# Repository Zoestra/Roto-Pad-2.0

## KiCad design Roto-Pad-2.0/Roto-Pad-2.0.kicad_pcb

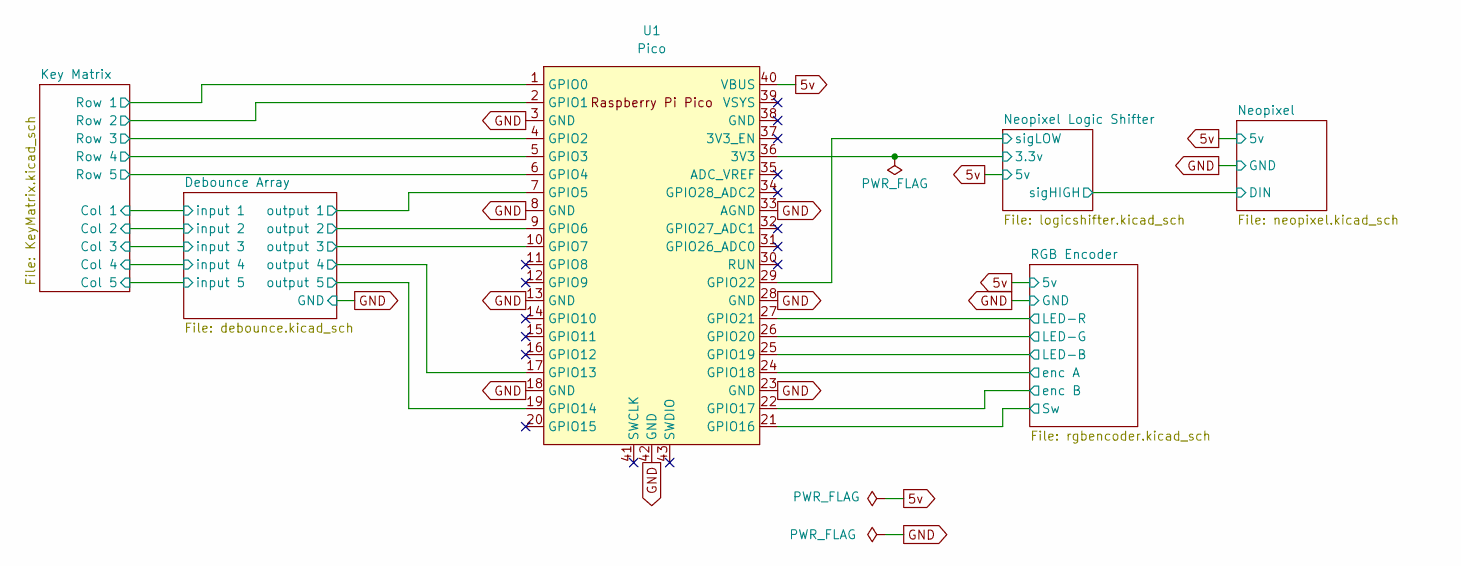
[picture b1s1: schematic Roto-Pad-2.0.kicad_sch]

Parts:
U1: Pico; raspberry_pi_pico_THT

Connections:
5v: U1.40 (VBUS); also elsewhere on the board
/Debounce Array/output 1: U1.7 (GPIO5); also elsewhere on the board
/Debounce Array/output 2: U1.9 (GPIO6); also elsewhere on the board
/Debounce Array/output 3: U1.10 (GPIO7); also elsewhere on the board
/Debounce Array/output 4: U1.17 (GPIO13); also elsewhere on the board
/Debounce Array/output 5: U1.19 (GPIO14); also elsewhere on the board
/Key Matrix/Row 1: U1.1 (GPIO0); also elsewhere on the board
/Key Matrix/Row 2: U1.2 (GPIO1); also elsewhere on the board
/Key Matrix/Row 3: U1.4 (GPIO2); also elsewhere on the board
/Key Matrix/Row 4: U1.5 (GPIO3); also elsewhere on the board
/Key Matrix/Row 5: U1.6 (GPIO4); also elsewhere on the board
/Neopixel Logic Shifter/3.3v: U1.36 (3V3); also elsewhere on the board
/Neopixel Logic Shifter/sigLOW: U1.29 (GPIO22); also elsewhere on the board
/RGB Encoder/LED-B: U1.25 (GPIO19); also elsewhere on the board
/RGB Encoder/LED-G: U1.26 (GPIO20); also elsewhere on the board
/RGB Encoder/LED-R: U1.27 (GPIO21); also elsewhere on the board
/RGB Encoder/Sw: U1.21 (GPIO16); also elsewhere on the board
/RGB Encoder/enc A: U1.24 (GPIO18); also elsewhere on the board
/RGB Encoder/enc B: U1.22 (GPIO17); also elsewhere on the board
GND: U1.3 (GND), U1.8 (GND), U1.13 (GND), U1.18 (GND), U1.23 (GND), U1.28 (GND), U1.33 (AGND), U1.42 (GND); also elsewhere on the board

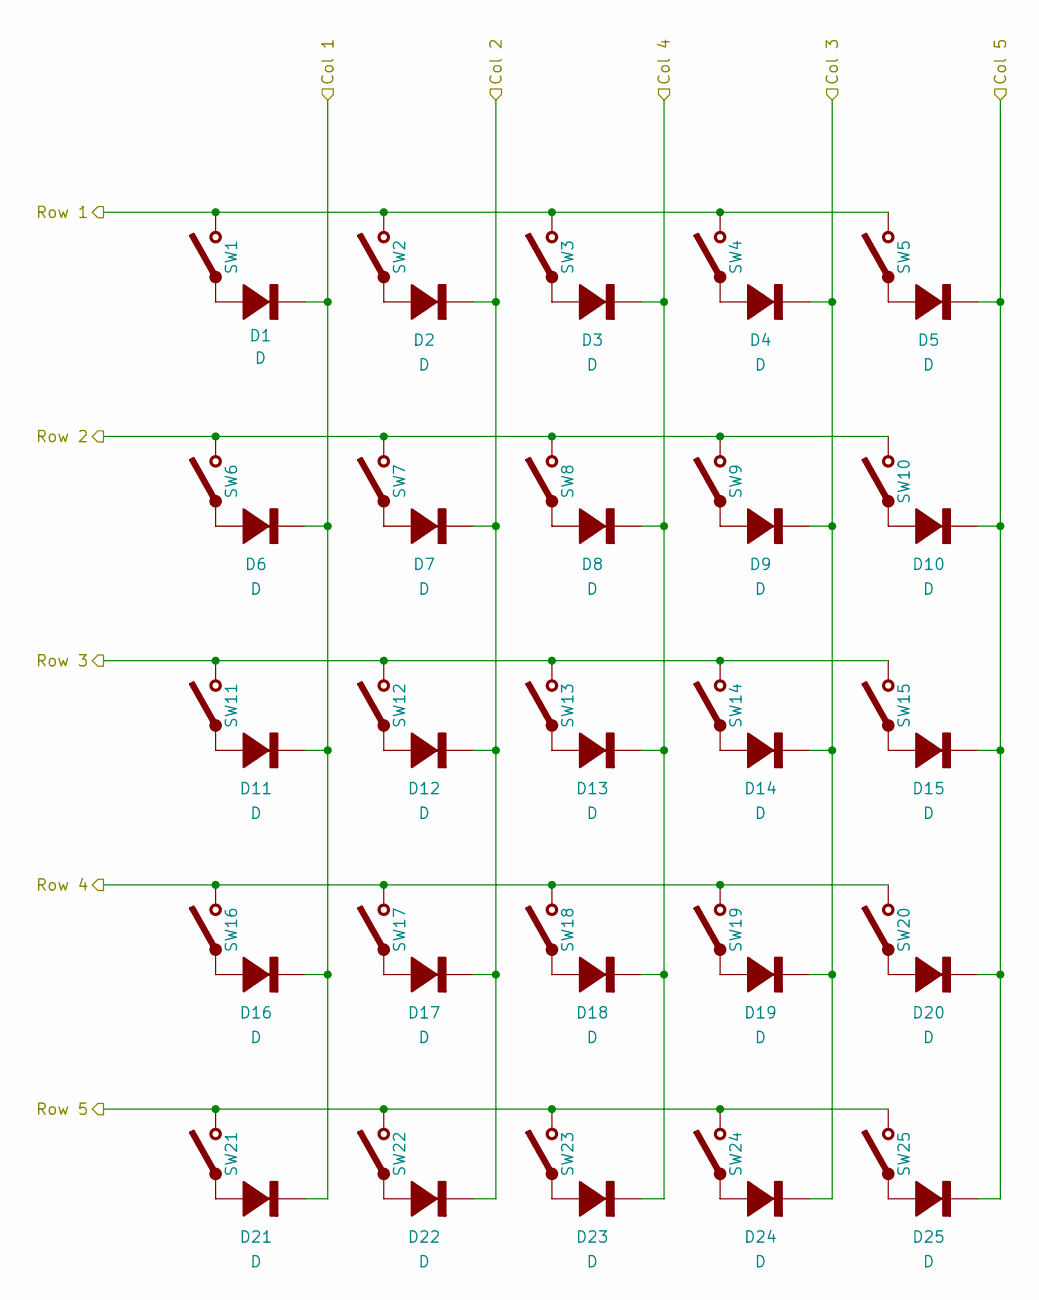
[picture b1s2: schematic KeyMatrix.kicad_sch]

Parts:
D1, D2, D3, D4, D5, D6, D7, D8, D9, D10, D11, D12, D13, D14, D15, D16, D17, D18, D19, D20, D21, D22, D23, D24, D25: D; D_SMA; Rating V/A
SW1, SW2, SW3, SW4, SW5, SW6, SW7, SW8, SW9, SW10, SW11, SW12, SW13, SW14, SW15, SW16, SW17, SW18, SW19, SW20, SW21, SW22, SW23, SW24, SW25: Switch; SW_Hotswap_Kailh_MX_1.00u

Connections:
/Debounce Array/input 1: D1.1 (K-), D6.1 (K-), D11.1 (K-), D16.1 (K-), D21.1 (K-); also elsewhere on the board
/Debounce Array/input 2: D2.1 (K-), D7.1 (K-), D12.1 (K-), D17.1 (K-), D22.1 (K-); also elsewhere on the board
/Debounce Array/input 3: D4.1 (K-), D9.1 (K-), D14.1 (K-), D19.1 (K-), D24.1 (K-); also elsewhere on the board
/Debounce Array/input 4: D3.1 (K-), D8.1 (K-), D13.1 (K-), D18.1 (K-), D23.1 (K-); also elsewhere on the board
/Debounce Array/input 5: D5.1 (K-), D10.1 (K-), D15.1 (K-), D20.1 (K-), D25.1 (K-); also elsewhere on the board
/Key Matrix/Row 1: SW1.1, SW2.1, SW3.1, SW4.1, SW5.1; also elsewhere on the board
/Key Matrix/Row 2: SW6.1, SW7.1, SW8.1, SW9.1, SW10.1; also elsewhere on the board
/Key Matrix/Row 3: SW11.1, SW12.1, SW13.1, SW14.1, SW15.1; also elsewhere on the board
/Key Matrix/Row 4: SW16.1, SW17.1, SW18.1, SW19.1, SW20.1; also elsewhere on the board
/Key Matrix/Row 5: SW21.1, SW22.1, SW23.1, SW24.1, SW25.1; also elsewhere on the board
unnamed: D1.2 (A+), SW1.2
unnamed: D2.2 (A+), SW2.2
unnamed: D3.2 (A+), SW3.2
unnamed: D4.2 (A+), SW4.2
unnamed: D5.2 (A+), SW5.2
unnamed: D6.2 (A+), SW6.2
unnamed: D7.2 (A+), SW7.2
unnamed: D8.2 (A+), SW8.2
unnamed: D9.2 (A+), SW9.2
unnamed: D10.2 (A+), SW10.2
unnamed: D11.2 (A+), SW11.2
unnamed: D12.2 (A+), SW12.2
unnamed: D13.2 (A+), SW13.2
unnamed: D14.2 (A+), SW14.2
unnamed: D15.2 (A+), SW15.2
unnamed: D16.2 (A+), SW16.2
unnamed: D17.2 (A+), SW17.2
unnamed: D18.2 (A+), SW18.2
unnamed: D19.2 (A+), SW19.2
unnamed: D20.2 (A+), SW20.2
unnamed: D21.2 (A+), SW21.2
unnamed: D22.2 (A+), SW22.2
unnamed: D23.2 (A+), SW23.2
unnamed: D24.2 (A+), SW24.2
unnamed: D25.2 (A+), SW25.2

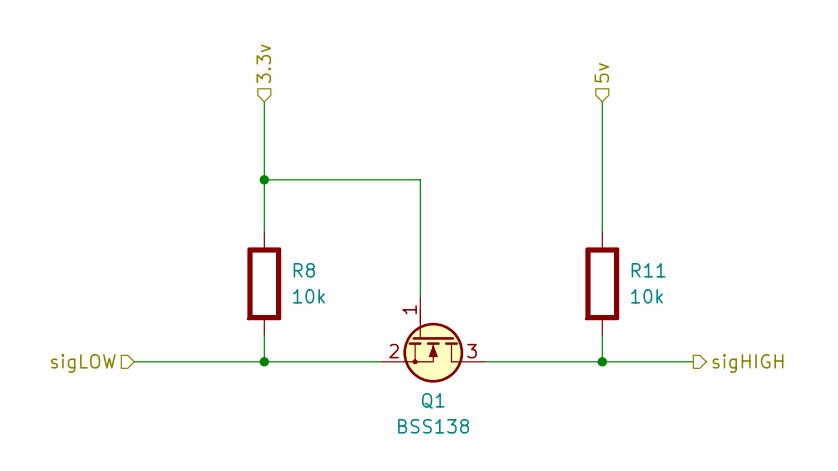
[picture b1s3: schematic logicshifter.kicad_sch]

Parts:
Q1: BSS138; SOT-23
R8, R11: 10k; R_0402; Rating W

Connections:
5v: R11.1 (+); also elsewhere on the board
/Neopixel Logic Shifter/3.3v: Q1.1 (G), R8.1 (+); also elsewhere on the board
/Neopixel Logic Shifter/sigHIGH: Q1.3 (D), R11.2 (-); also elsewhere on the board
/Neopixel Logic Shifter/sigLOW: Q1.2 (S), R8.2 (-); also elsewhere on the board

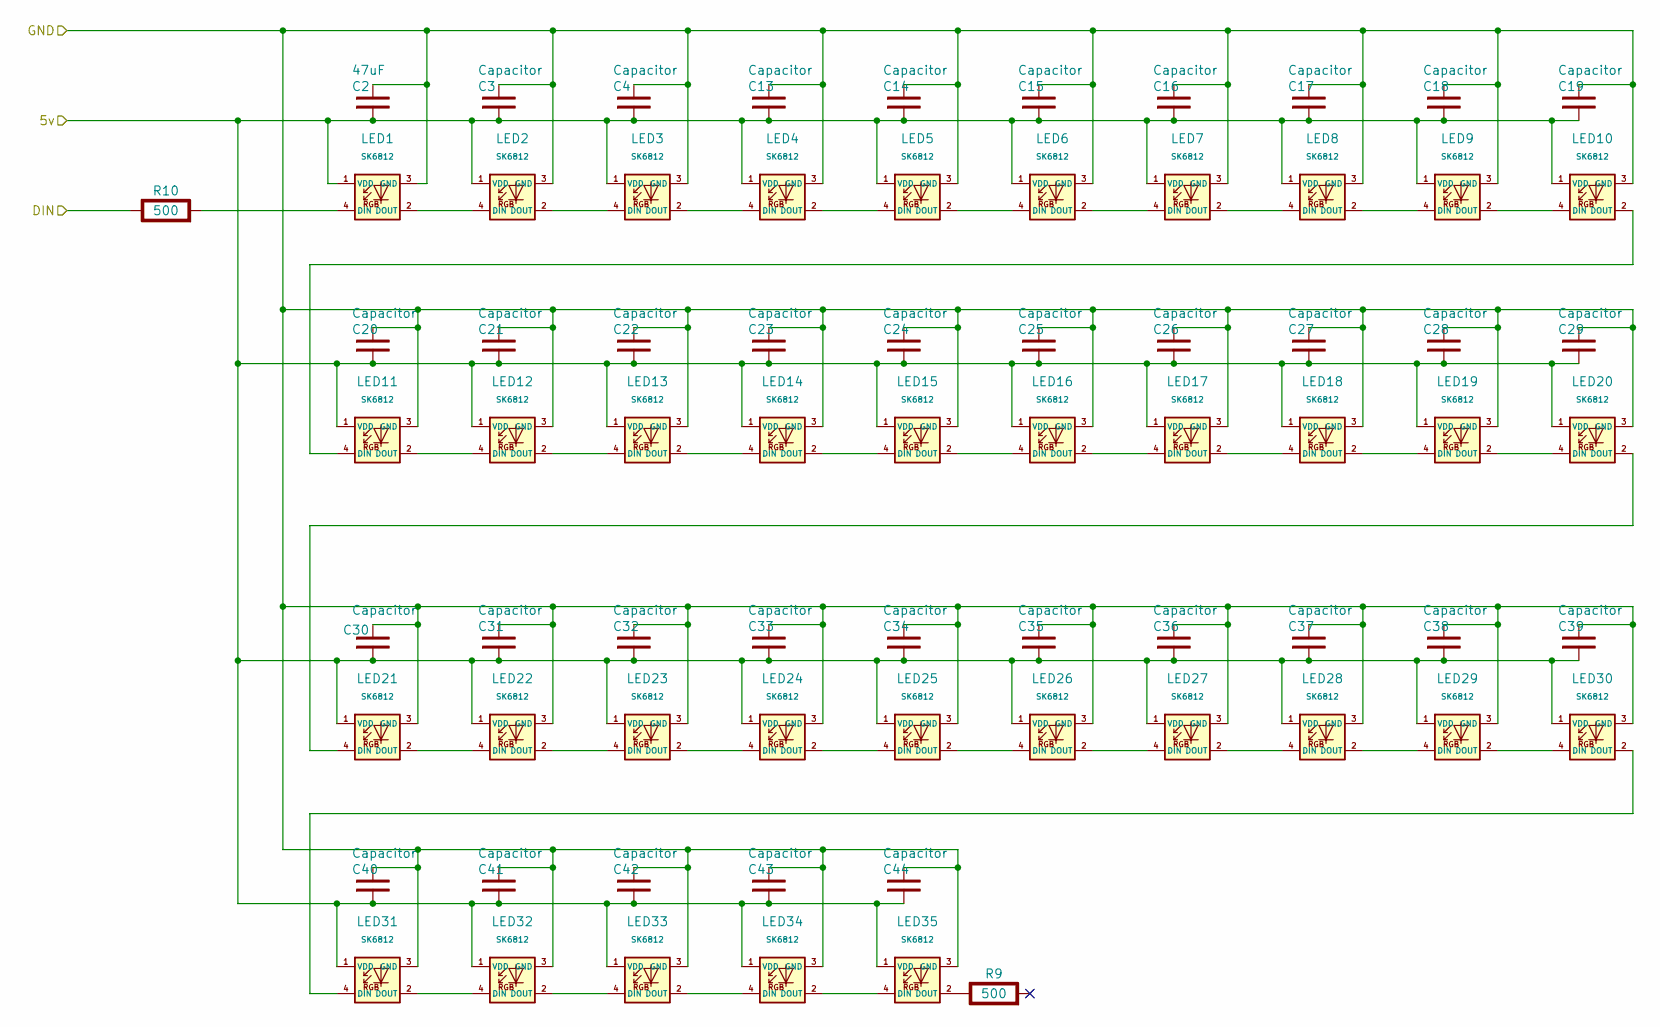
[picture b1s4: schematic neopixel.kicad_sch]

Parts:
C2: 47uF; 0805
C3, C4, C13, C14, C15, C16, C17, C18, C19, C20, C21, C22, C23, C24, C25, C26, C27, C28, C29, C30, C31, C32, C33, C34, C35, C36, C37, C38, C39, C40, C41, C42, C43, C44: Capacitor; 0805
LED1, LED2, LED3, LED4, LED5, LED6, LED7, LED8, LED9, LED10, LED11, LED12, LED13, LED14, LED15, LED16, LED17, LED18, LED19, LED20, LED21, LED22, LED23, LED24, LED25: SK6812; SK6812-Mini-E MX
LED26, LED27, LED28, LED29, LED30, LED31, LED32, LED33, LED34, LED35: SK6812; LED_SK6812_PLCC4_5.0x5.0mm_P3.2mm
R9, R10: 500; R1206; Rating W

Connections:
5v: C2.1, C3.1, C4.1, C13.1, C14.1, C15.1, C16.1, C17.1, C18.1, C19.1, C20.1, C21.1, C22.1, C23.1, C24.1, C25.1, C26.1, C27.1, C28.1, C29.1, C30.1, C31.1, C32.1, C33.1, C34.1, C35.1, C36.1, C37.1, C38.1, C39.1, C40.1, C41.1, C42.1, C43.1, C44.1, LED1.1 (VDD), LED2.1 (VDD), LED3.1 (VDD), LED4.1 (VDD), LED5.1 (VDD), LED6.1 (VDD), LED7.1 (VDD), LED8.1 (VDD), LED9.1 (VDD), LED10.1 (VDD), LED11.1 (VDD), LED12.1 (VDD), LED13.1 (VDD), LED14.1 (VDD), LED15.1 (VDD), LED16.1 (VDD), LED17.1 (VDD), LED18.1 (VDD), LED19.1 (VDD), LED20.1 (VDD), LED21.1 (VDD), LED22.1 (VDD), LED23.1 (VDD), LED24.1 (VDD), LED25.1 (VDD), LED26.1 (VDD), LED27.1 (VDD), LED28.1 (VDD), LED29.1 (VDD), LED30.1 (VDD), LED31.1 (VDD), LED32.1 (VDD), LED33.1 (VDD), LED34.1 (VDD), LED35.1 (VDD); also elsewhere on the board
/Neopixel Logic Shifter/sigHIGH: R10.1 (+); also elsewhere on the board
GND: C2.2, C3.2, C4.2, C13.2, C14.2, C15.2, C16.2, C17.2, C18.2, C19.2, C20.2, C21.2, C22.2, C23.2, C24.2, C25.2, C26.2, C27.2, C28.2, C29.2, C30.2, C31.2, C32.2, C33.2, C34.2, C35.2, C36.2, C37.2, C38.2, C39.2, C40.2, C41.2, C42.2, C43.2, C44.2, LED1.3 (GND), LED2.3 (GND), LED3.3 (GND), LED4.3 (GND), LED5.3 (GND), LED6.3 (GND), LED7.3 (GND), LED8.3 (GND), LED9.3 (GND), LED10.3 (GND), LED11.3 (GND), LED12.3 (GND), LED13.3 (GND), LED14.3 (GND), LED15.3 (GND), LED16.3 (GND), LED17.3 (GND), LED18.3 (GND), LED19.3 (GND), LED20.3 (GND), LED21.3 (GND), LED22.3 (GND), LED23.3 (GND), LED24.3 (GND), LED25.3 (GND), LED26.3 (GND), LED27.3 (GND), LED28.3 (GND), LED29.3 (GND), LED30.3 (GND), LED31.3 (GND), LED32.3 (GND), LED33.3 (GND), LED34.3 (GND), LED35.3 (GND); also elsewhere on the board
unnamed: LED1.4 (DIN), R10.2 (-)
unnamed: LED1.2 (DOUT), LED2.4 (DIN)
unnamed: LED2.2 (DOUT), LED3.4 (DIN)
unnamed: LED3.2 (DOUT), LED4.4 (DIN)
unnamed: LED4.2 (DOUT), LED5.4 (DIN)
unnamed: LED5.2 (DOUT), LED6.4 (DIN)
unnamed: LED6.2 (DOUT), LED7.4 (DIN)
unnamed: LED7.2 (DOUT), LED8.4 (DIN)
unnamed: LED8.2 (DOUT), LED9.4 (DIN)
unnamed: LED9.2 (DOUT), LED10.4 (DIN)
unnamed: LED10.2 (DOUT), LED11.4 (DIN)
unnamed: LED11.2 (DOUT), LED12.4 (DIN)
unnamed: LED12.2 (DOUT), LED13.4 (DIN)
unnamed: LED13.2 (DOUT), LED14.4 (DIN)
unnamed: LED14.2 (DOUT), LED15.4 (DIN)
unnamed: LED15.2 (DOUT), LED16.4 (DIN)
unnamed: LED16.2 (DOUT), LED17.4 (DIN)
unnamed: LED17.2 (DOUT), LED18.4 (DIN)
unnamed: LED18.2 (DOUT), LED19.4 (DIN)
unnamed: LED19.2 (DOUT), LED20.4 (DIN)
unnamed: LED20.2 (DOUT), LED21.4 (DIN)
unnamed: LED21.2 (DOUT), LED22.4 (DIN)
unnamed: LED22.2 (DOUT), LED23.4 (DIN)
unnamed: LED23.2 (DOUT), LED24.4 (DIN)
unnamed: LED24.2 (DOUT), LED25.4 (DIN)
unnamed: LED25.2 (DOUT), LED26.4 (DIN)
unnamed: LED26.2 (DOUT), LED27.4 (DIN)
unnamed: LED27.2 (DOUT), LED28.4 (DIN)
unnamed: LED28.2 (DOUT), LED29.4 (DIN)
unnamed: LED29.2 (DOUT), LED30.4 (DIN)
unnamed: LED30.2 (DOUT), LED31.4 (DIN)
unnamed: LED31.2 (DOUT), LED32.4 (DIN)
unnamed: LED32.2 (DOUT), LED33.4 (DIN)
unnamed: LED33.2 (DOUT), LED34.4 (DIN)
unnamed: LED34.2 (DOUT), LED35.4 (DIN)
unnamed: LED35.2 (DOUT), R9.1 (+)

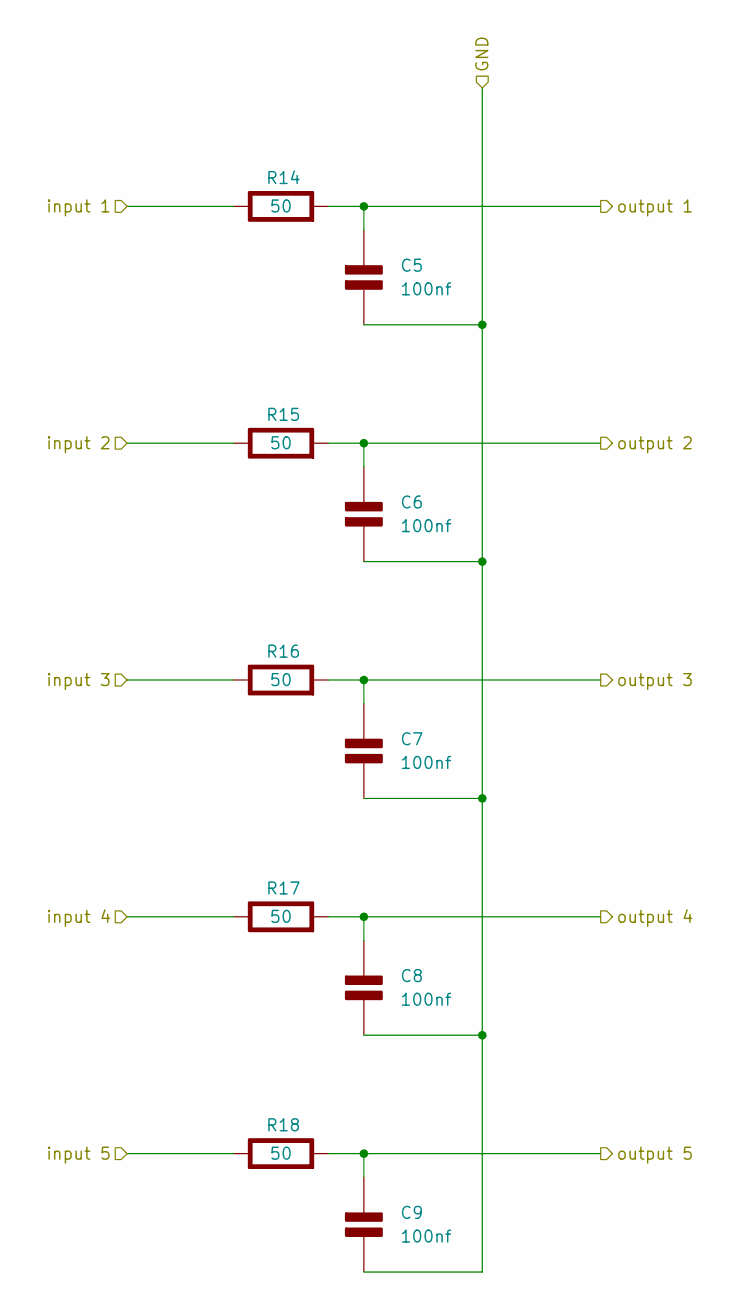
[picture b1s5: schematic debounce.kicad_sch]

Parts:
C5, C6, C7, C8, C9: 100nf; C_0402; Rating V
R14, R15, R16, R17, R18: 50; R0805; Rating W

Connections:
/Debounce Array/input 1: R14.1 (+); also elsewhere on the board
/Debounce Array/input 2: R15.1 (+); also elsewhere on the board
/Debounce Array/input 3: R16.1 (+); also elsewhere on the board
/Debounce Array/input 4: R17.1 (+); also elsewhere on the board
/Debounce Array/input 5: R18.1 (+); also elsewhere on the board
/Debounce Array/output 1: C5.1 (+), R14.2 (-); also elsewhere on the board
/Debounce Array/output 2: C6.1 (+), R15.2 (-); also elsewhere on the board
/Debounce Array/output 3: C7.1 (+), R16.2 (-); also elsewhere on the board
/Debounce Array/output 4: C8.1 (+), R17.2 (-); also elsewhere on the board
/Debounce Array/output 5: C9.1 (+), R18.2 (-); also elsewhere on the board
GND: C5.2 (-), C6.2 (-), C7.2 (-), C8.2 (-), C9.2 (-); also elsewhere on the board

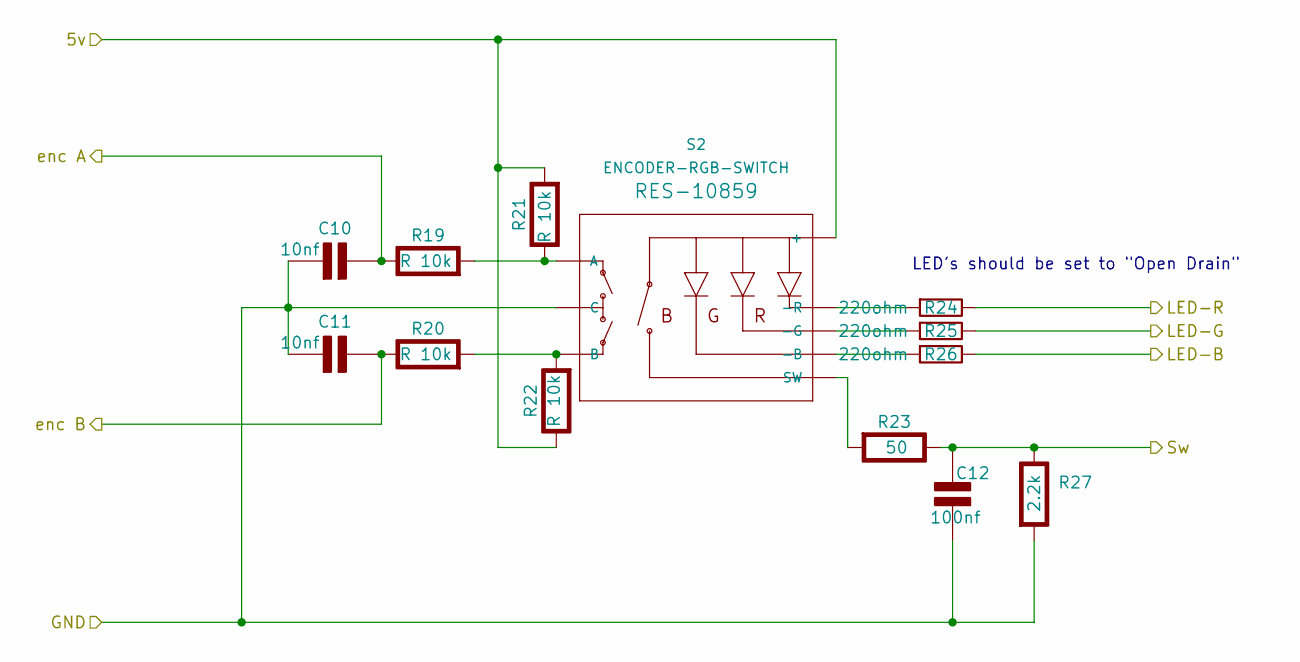
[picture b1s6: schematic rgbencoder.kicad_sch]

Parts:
C10, C11: 10nf; C_0402; Rating V
C12: 100nf; C_0402; Rating V
R19, R20, R21, R22: R 10k; R_0402; Rating W
R23: 50; R0805; Rating W
R24, R25, R26: 220ohm; R1206
R27: 2.2k; R_0402; Rating W
S2: ENCODER-RGB-SWITCH; Led Encoder

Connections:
5v: R21.2 (-), R22.1 (+), S2.5 (+); also elsewhere on the board
/RGB Encoder/LED-B: R26.2; also elsewhere on the board
/RGB Encoder/LED-G: R25.2; also elsewhere on the board
/RGB Encoder/LED-R: R24.2; also elsewhere on the board
/RGB Encoder/Sw: C12.2 (-), R23.1 (+), R27.1 (+); also elsewhere on the board
/RGB Encoder/enc A: C10.2 (-), R19.1 (+); also elsewhere on the board
/RGB Encoder/enc B: C11.2 (-), R20.1 (+); also elsewhere on the board
GND: C10.1 (+), C11.1 (+), C12.1 (+), R27.2 (-), S2.C; also elsewhere on the board
unnamed: R19.2 (-), R21.1 (+), S2.A
unnamed: R20.2 (-), R22.2 (-), S2.B
unnamed: R23.2 (-), S2.3 (SW)
unnamed: R26.1, S2.4 (-B)
unnamed: R25.1, S2.2 (-G)
unnamed: R24.1, S2.1 (-R)

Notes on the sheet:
LED's should be set to "Open Drain"

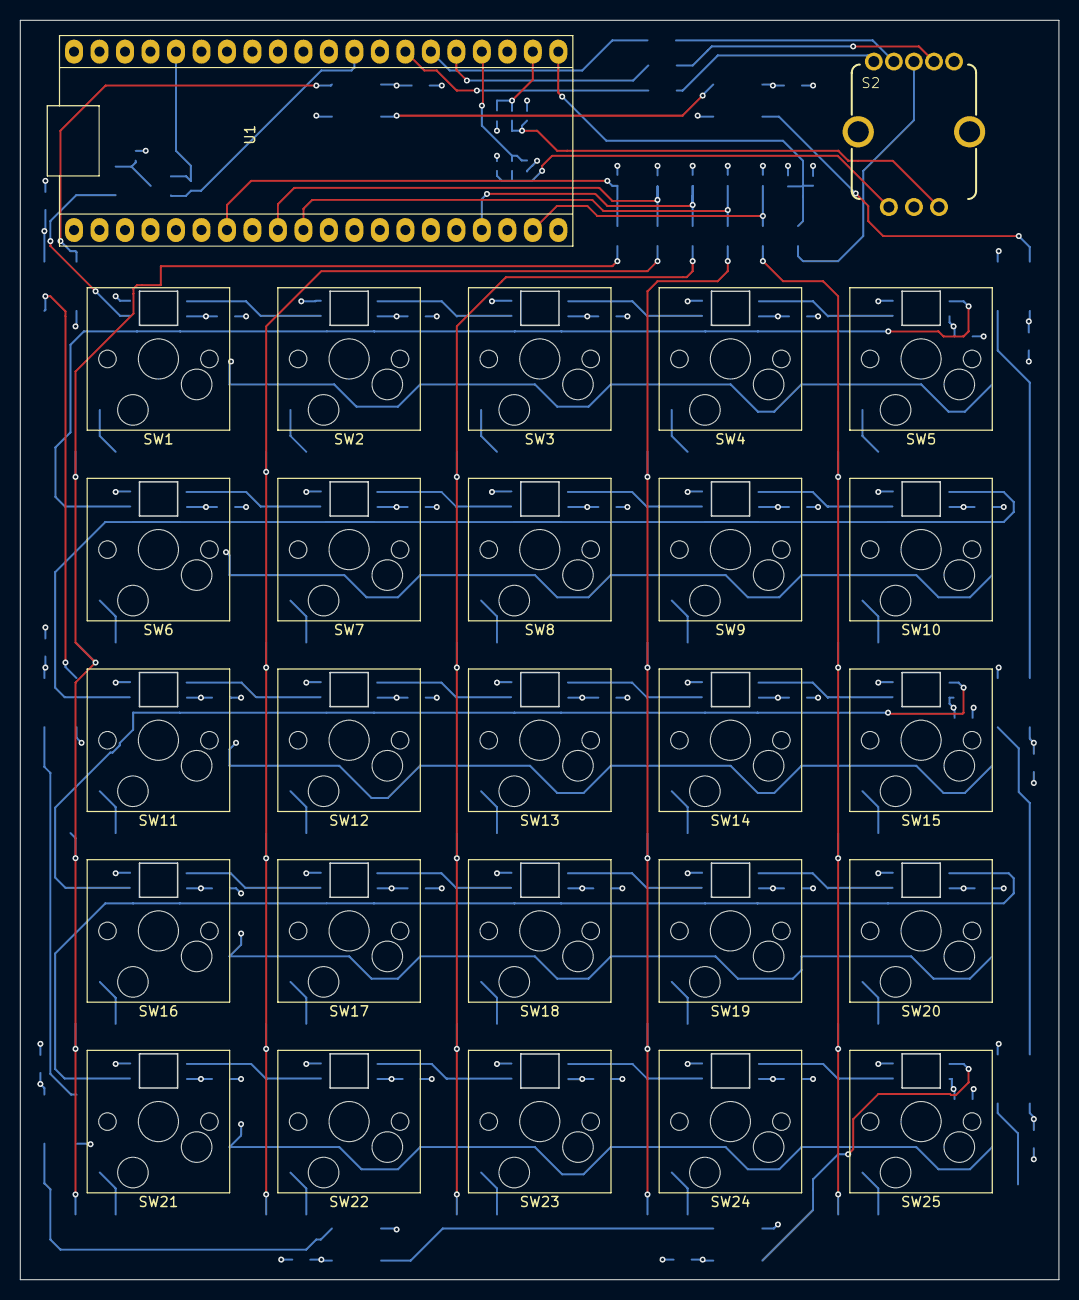
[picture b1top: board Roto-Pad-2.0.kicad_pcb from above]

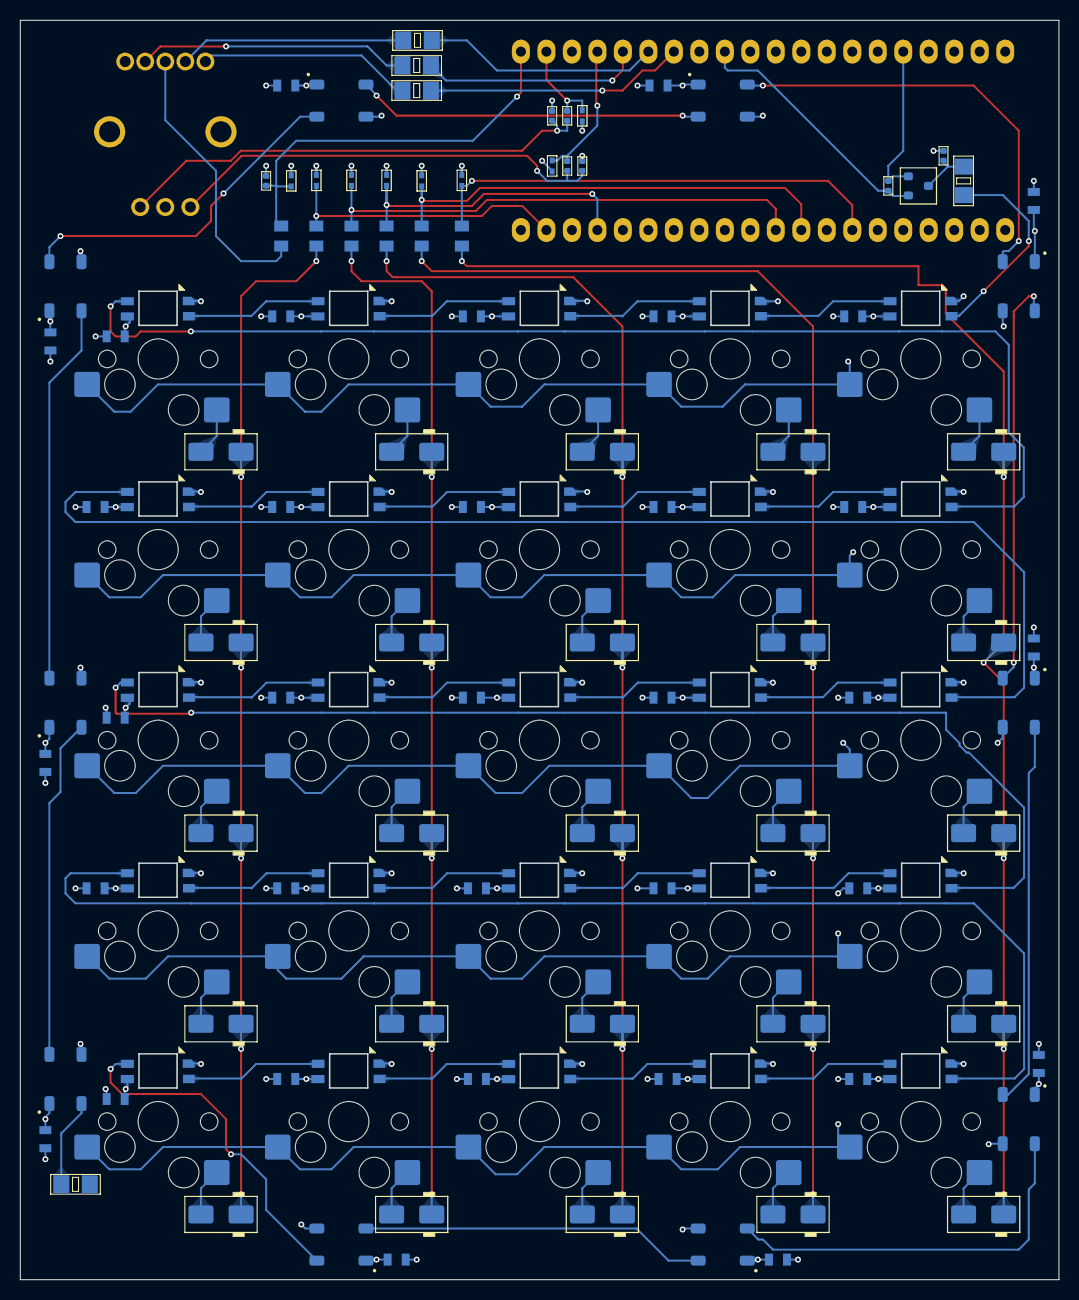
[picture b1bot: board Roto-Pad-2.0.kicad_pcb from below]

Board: 4 copper layers, 103.4 x 125.4 mm, 149 parts (97 on the bottom side), 93 nets.

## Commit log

2025-03-07 created repo
2025-03-07 completed schematic, passes ERC
2025-03-07 completed physical PCB layout
2025-03-10 added more heirarchical sheets, debouncing
2025-03-11 layout completed, first draft of routing
2025-03-31 finished initial routing
2025-03-31 PCB passes DRC
